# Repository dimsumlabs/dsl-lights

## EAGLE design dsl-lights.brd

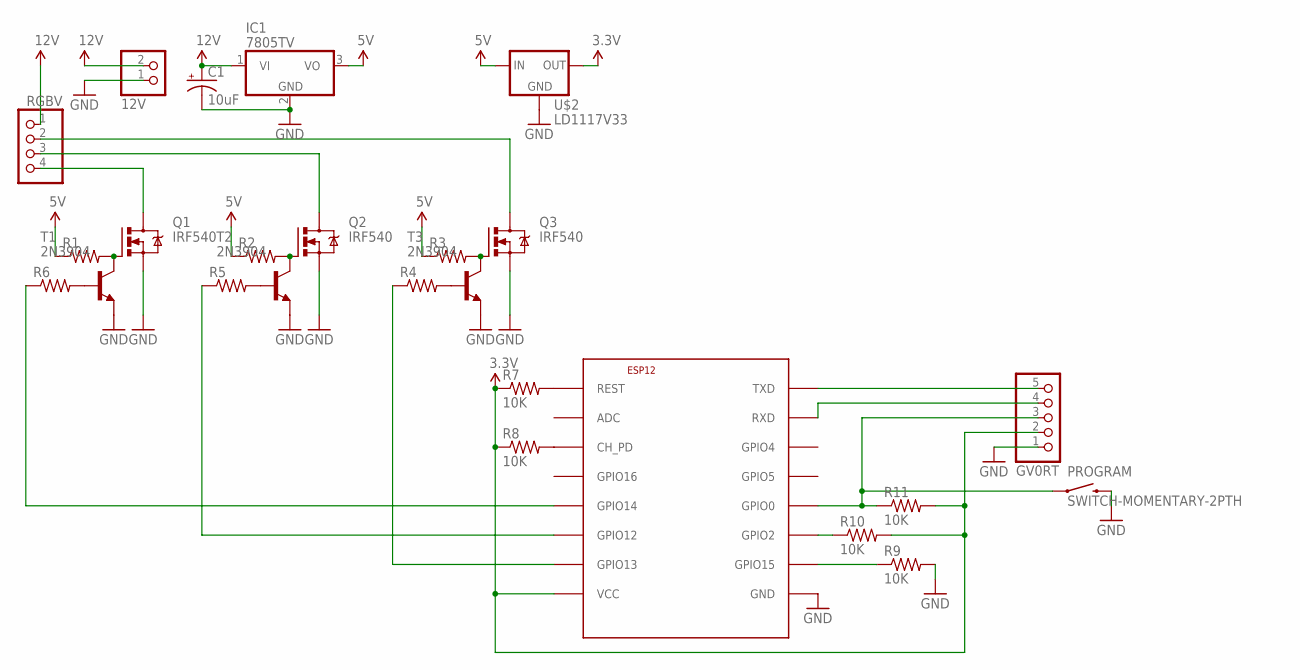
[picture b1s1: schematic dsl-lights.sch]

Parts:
12V: HEADER-1X2; 1X02_OVAL
C1: 10uF; CPOL-RADIAL-100UF-25V
ESP12: ESP8266-12; ESP-12
GV0RT: HEADER-1X5; 1X05_OVAL
IC1: 7805TV; TO220V
PROGRAM: SWITCH-MOMENTARY-2PTH; TACTILE-PTH
Q1, Q2, Q3: IRF540; TO220BV
R1, R2, R3, R4, R5, R6: RESISTORAXIAL-0.3; AXIAL-0.3
R7, R8, R9, R10, R11: 10K; AXIAL-0.3
RGBV: HEADER-1X4; 1X04_OVAL
T1, T2, T3: 2N3904; TO92
U$2: LD1117V33; 78XXL

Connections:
3.3V: ESP12.VCC, GV0RT.2, R7.P$1 (1), R8.P$1 (1), R10.P$2 (2), R11.P$2 (2), U$2.GND (OUT)
5V: IC1.3 (VO), R1.P$1 (1), R2.P$1 (1), R3.P$1 (1), U$2.OUT (IN)
12V: 12V.2, C1.1 (+), IC1.1 (VI), RGBV.1
GND: 12V.1, C1.2 (-), ESP12.GND, GV0RT.1, IC1.2 (GND), PROGRAM.3 (2), Q1.S, Q2.S, Q3.S, R9.P$2 (2), T1.3 (E), T2.3 (E), T3.3 (E), U$2.IN (GND)
unnamed: Q2.G, R2.P$2 (2), T2.1 (C)
unnamed: Q3.G, R3.P$2 (2), T3.1 (C)
unnamed: Q1.G, R1.P$2 (2), T1.1 (C)
unnamed: R4.P$2 (2), T3.2 (B)
unnamed: R5.P$2 (2), T2.2 (B)
unnamed: R6.P$2 (2), T1.2 (B)
unnamed: Q1.D, RGBV.4
unnamed: Q2.D, RGBV.3
unnamed: Q3.D, RGBV.2
unnamed: ESP12.GPIO14, R6.P$1 (1)
unnamed: ESP12.GPIO12, R5.P$1 (1)
unnamed: ESP12.GPIO13, R4.P$1 (1)
unnamed: ESP12.REST, R7.P$2 (2)
unnamed: ESP12.CH_PD, R8.P$2 (2)
unnamed: ESP12.GPIO15, R9.P$1 (1)
unnamed: ESP12.GPIO2, R10.P$1 (1)
unnamed: ESP12.GPIO0, GV0RT.3, PROGRAM.1, R11.P$1 (1)
unnamed: ESP12.TXD, GV0RT.5
unnamed: ESP12.RXD, GV0RT.4

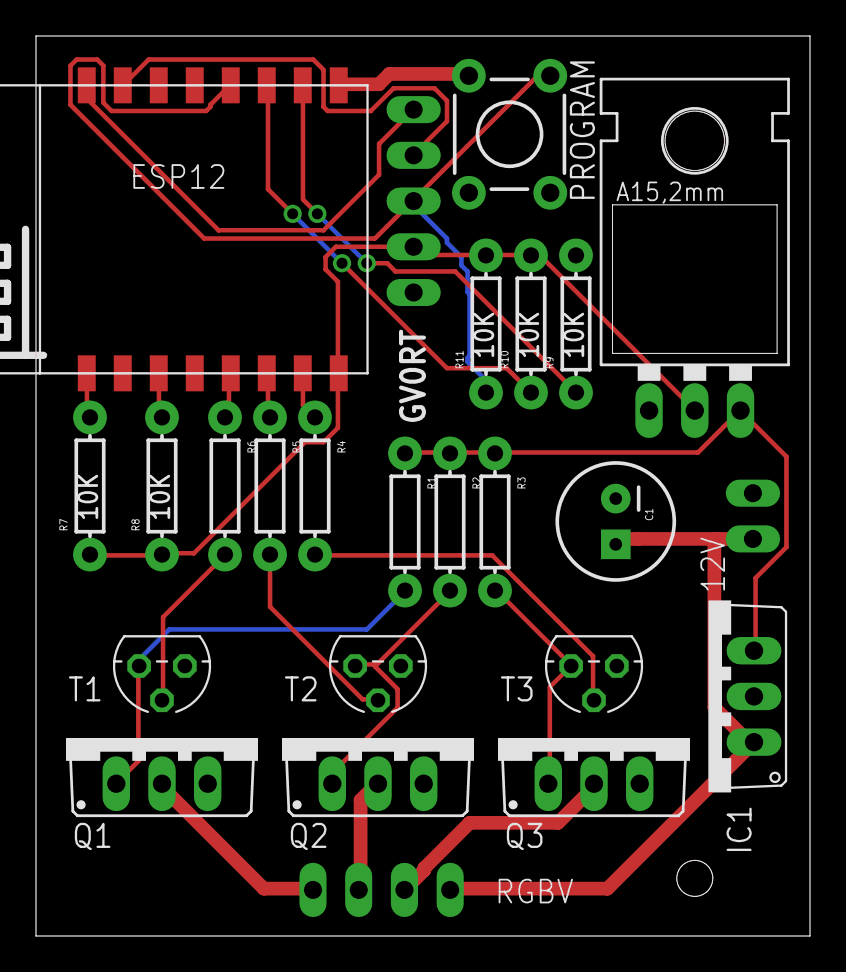
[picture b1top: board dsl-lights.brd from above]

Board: 2 copper layers, 43.0 x 50.0 mm, 25 parts (0 on the bottom side), 23 nets.

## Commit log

2015-10-27 Initial
2016-07-19 Added lights branch of nodemcu-httpd

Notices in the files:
parts and their libraries:
microbuilder: This work is placed in the public domain, and may be freely used for commercial and non-commercial work with the following conditions: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
SparkFun-Passives: Licensing: Creative Commons ShareAlike 4.0 International - https://creativecommons.org/licenses/by-sa/4.0
